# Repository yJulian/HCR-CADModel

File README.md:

From
https://github.com/open-dynamic-robot-initiative/master-board

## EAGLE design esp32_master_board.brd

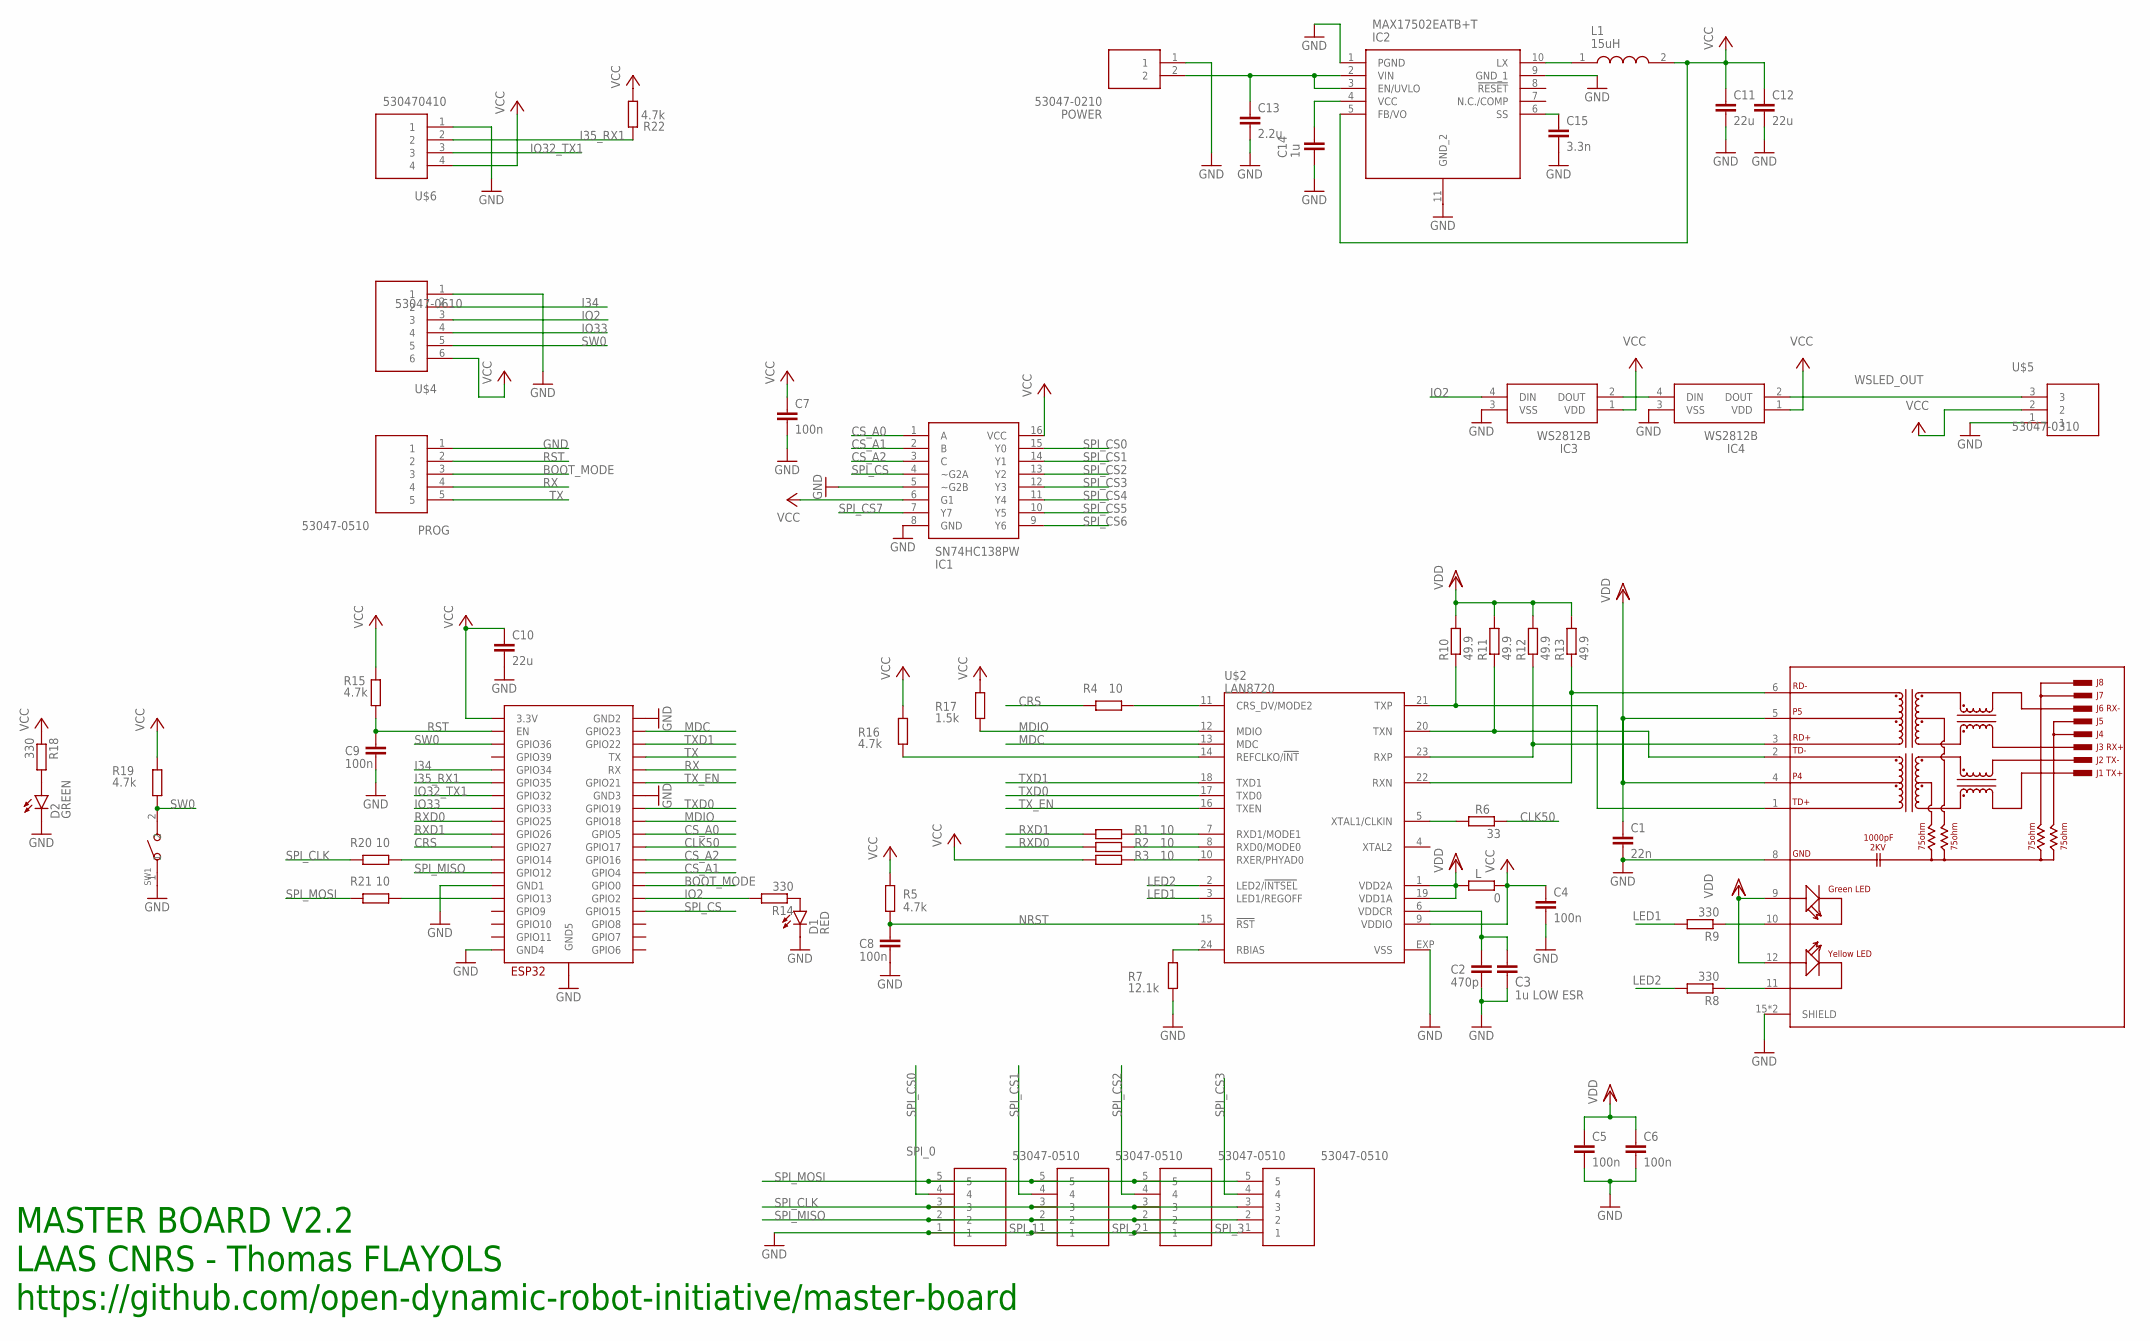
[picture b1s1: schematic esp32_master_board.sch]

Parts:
C1: 22n; 0402; MANUFACTURER_PART_NUMBER 885012205052
C2: 470p; 0402; MANUFACTURER_PART_NUMBER CL05C471JB5NNNC
C3: 1u LOW ESR; 0402; MANUFACTURER_PART_NUMBER CPL-CAP-X5R-0402-1UF-6.3V
C4, C5, C6, C7, C8, C9: 100n; 0402; MANUFACTURER_PART_NUMBER CPL-CAP-X7R-0402-100NF-16V
C10, C11, C12: 22u; C0805; MANUFACTURER_PART_NUMBER CPL-CAP-X5R-0805-22UF-6.3V
C13: 2.2u; C1210; MANUFACTURER_PART_NUMBER C3225X7R1H225K250AB
C14: 1u; 0402; MANUFACTURER_PART_NUMBER CPL-CAP-X5R-0402-1UF-6.3V
C15: 3.3n; 0402; MANUFACTURER_PART_NUMBER 885012205064
D1: RED; CHIPLED_0603; MANUFACTURER_PART_NUMBER CPL-LED-0603-RED
D2: GREEN; CHIPLED_0603; MANUFACTURER_PART_NUMBER CPL-LED-0603-GREEN
IC1: SN74HC138PW; SOP65P640X120-16N
IC2: MAX17502EATB+T; SON50P200X300X80-11N
IC3, IC4: WS2812B
L: 0; 0402; MANUFACTURER_PART_NUMBER CPL-RES-0402-0-0.063W
L1: 15uH; LPS6235
POWER: 53047-0210; 530470210; MANUFACTURER_PART_NUMBER DF13-3P-1.25DSA
PROG: 53047-0510; 530470510; MANUFACTURER_PART_NUMBER DF13-5P-1.25DSA
R1, R2, R3, R4, R20, R21: 10; 0402; MANUFACTURER_PART_NUMBER CPL-RES-0402-10-0.063W
R5, R15, R16, R19, R22: 4.7k; 0402; MANUFACTURER_PART_NUMBER CPL-RES-0402-4.7K-0.063W
R6: 33; 0402; MANUFACTURER_PART_NUMBER CRCW040233R0FKEDC
R7: 12.1k; 0402; MANUFACTURER_PART_NUMBER ERJ-U02F1212X
R8, R9, R14, R18: 330; 0402; MANUFACTURER_PART_NUMBER RC0402JR-13330RL
R10, R11, R12, R13: 49.9; 0402; MANUFACTURER_PART_NUMBER CRCW040249R9FKEDC
R17: 1.5k; 0402; MANUFACTURER_PART_NUMBER ERJ2GEJ152X
SPI_0, SPI_1, SPI_2, SPI_3: 53047-0510; 530470510; MANUFACTURER_PART_NUMBER DF13-5P-1.25DSA
SW1: B3U-1000P-2P-SMD; SW2-2.6-3.0X2.5X1.2+0.4MM; MANUFACTURER_PART_NUMBER B3U-1000P
U$1: ESP32-WROOM; MANUFACTURER_PART_NUMBER ESP32-WROOM-32D
U$2: LAN8720; QFN24; MANUFACTURER_PART_NUMBER LAN8720A-CP
U$3: HR911105A; HANRUN_HR911105A; MANUFACTURER_PART_NUMBER HR911105A
U$4: 53047-0610; 530470610; MANUFACTURER_PART_NUMBER DF13-6P-1.25DSA
U$5: 53047-0310; 530470310; MANUFACTURER_PART_NUMBER DF13-3P-1.25DSA
U$6: 530470410; MANUFACTURER_PART_NUMBER DF13-4P-1.25DSA

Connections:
BOOT_MODE: PROG.3, U$1.IO0 (GPIO0)
CLK50: R6.1, U$1.IO17 (GPIO17)
CRS: R4.1, U$1.IO27 (GPIO27)
CS_A0: IC1.1 (A), U$1.IO5 (GPIO5)
CS_A1: IC1.2 (B), U$1.IO4 (GPIO4)
CS_A2: IC1.3 (C), U$1.IO16 (GPIO16)
GND: C1.2, C2.2, C3.2, C4.2, C5.2, C6.2, C7.2, C8.2, C9.2, C10.2, C11.2, C12.2, C13.2, C14.1, C15.2, D1.C, D2.C, IC1.5 (~G2B), IC1.8 (GND), IC2.1 (PGND), IC2.9 (GND_1), IC2.11 (GND_2), IC3.3 (VSS), IC4.3 (VSS), POWER.1, PROG.1, R7.1, SPI_0.1, SPI_1.1, SPI_2.1, SPI_3.1, SW1.1, U$1.GND1, U$1.GND2, U$1.GND3, U$1.GND4, U$1.GND5, U$2.EXP (VSS), U$3.8 (GND), U$3.15 (SHIELD), U$3.16 (SHIELD), U$4.1, U$5.1, U$6.1
I34: U$1.IO34 (GPIO34), U$4.2
I35_RX1: R22.2, U$1.IO35 (GPIO35), U$6.2
IO2: IC3.4 (DIN), R14.2, U$1.IO2 (GPIO2), U$4.3
IO32_TX1: U$1.IO32 (GPIO32), U$6.3
IO33: U$1.IO33 (GPIO33), U$4.4
LED1: R9.2, U$2.3 (LED1/REGOFF)
LED2: R8.2, U$2.2 (LED2/!INTSEL)
MDC: U$1.IO23 (GPIO23), U$2.13 (MDC)
MDIO: R17.1, U$1.IO18 (GPIO18), U$2.12 (MDIO)
unnamed: R1.2, U$2.7 (RXD1/MODE1)
unnamed: R2.2, U$2.8 (RXD0/MODE0)
unnamed: R3.2, U$2.10 (RXER/PHYAD0)
unnamed: R4.2, U$2.11 (CRS_DV/MODE2)
unnamed: R6.2, U$2.5 (XTAL1/CLKIN)
unnamed: R7.2, U$2.24 (RBIAS)
unnamed: R10.1, U$2.21 (TXP), U$3.1 (TD+)
unnamed: R11.1, U$2.20 (TXN), U$3.2 (TD-)
unnamed: R12.1, U$2.23 (RXP), U$3.3 (RD+)
unnamed: R13.1, U$2.22 (RXN), U$3.6 (RD-)
unnamed: R8.1, U$3.11 (YC)
unnamed: R9.1, U$3.10 (GC)
unnamed: R16.1, U$2.14 (REFCLKO/!INT)
unnamed: C2.1, C3.1, U$2.6 (VDDCR)
unnamed: C14.2, IC2.4 (VCC)
unnamed: D1.A, R14.1
unnamed: R21.2, U$1.IO13 (GPIO13)
unnamed: IC2.10 (LX), L1.1
unnamed: IC3.2 (DOUT), IC4.4 (DIN)
unnamed: D2.A, R18.2
unnamed: R20.2, U$1.IO14 (GPIO14)
unnamed: C15.1, IC2.6 (SS)
unnamed: C13.1, IC2.2 (VIN), IC2.3 (EN/UVLO), POWER.2
NRST: C8.1, R5.1, U$2.15 (!RST)
RST: C9.1, PROG.2, R15.1, U$1.EN
RX: PROG.4, U$1.RX
RXD0: R2.1, U$1.IO25 (GPIO25)
RXD1: R1.1, U$1.IO26 (GPIO26)
SPI_CLK: R20.1, SPI_0.3, SPI_1.3, SPI_2.3, SPI_3.3
SPI_CS: IC1.4 (~G2A), U$1.IO15 (GPIO15)
SPI_CS0: IC1.15 (Y0), SPI_0.4
SPI_CS1: IC1.14 (Y1), SPI_1.4
SPI_CS2: IC1.13 (Y2), SPI_2.4
SPI_CS3: IC1.12 (Y3), SPI_3.4
SPI_CS4: IC1.11 (Y4)
SPI_CS5: IC1.10 (Y5)
SPI_CS6: IC1.9 (Y6)
SPI_CS7: IC1.7 (Y7)
SPI_MISO: SPI_0.2, SPI_1.2, SPI_2.2, SPI_3.2, U$1.IO12 (GPIO12)
SPI_MOSI: R21.1, SPI_0.5, SPI_1.5, SPI_2.5, SPI_3.5
SW0: R19.1, SW1.2, U$1.SENSOR_VP (GPIO36), U$4.5
TX: PROG.5, U$1.TX
TXD0: U$1.IO19 (GPIO19), U$2.17 (TXD0)
TXD1: U$1.IO22 (GPIO22), U$2.18 (TXD1)
TX_EN: U$1.IO21 (GPIO21), U$2.16 (TXEN)
VCC: C4.1, C7.1, C10.1, C11.1, C12.1, IC1.6 (G1), IC1.16 (VCC), IC2.5 (FB/VO), IC3.1 (VDD), IC4.1 (VDD), L.1, L1.2, R3.1, R5.2, R15.2, R16.2, R17.2, R18.1, R19.2, R22.1, U$1.3V3 (3.3V), U$2.9 (VDDIO), U$4.6, U$5.2, U$6.4
VDD: C1.1, C5.1, C6.1, L.2, R10.2, R11.2, R12.2, R13.2, U$2.1 (VDD2A), U$2.19 (VDD1A), U$3.4, U$3.5, U$3.9 (GA), U$3.12 (YA)
WSLED_OUT: IC4.2 (DOUT), U$5.3

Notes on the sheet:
MASTER BOARD V2.2 LAAS CNRS - Thomas FLAYOLS https://github.com/open-dynamic-robot-initiative/master-board

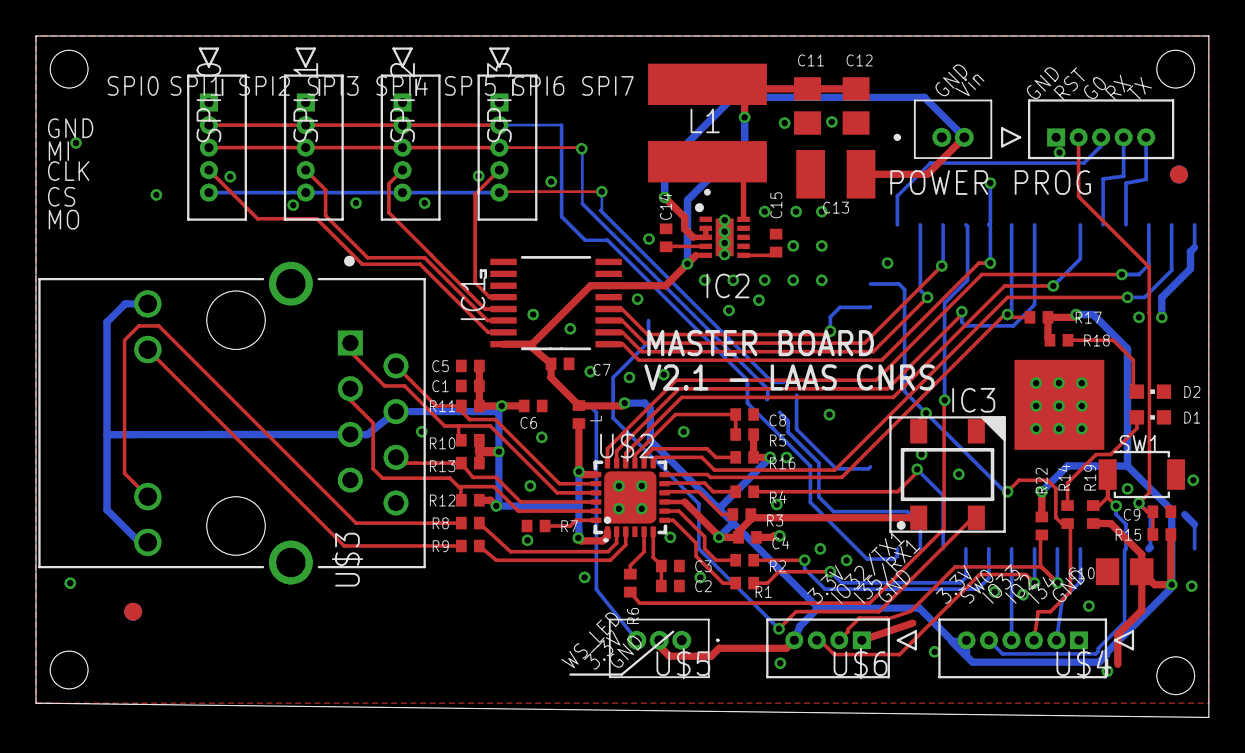
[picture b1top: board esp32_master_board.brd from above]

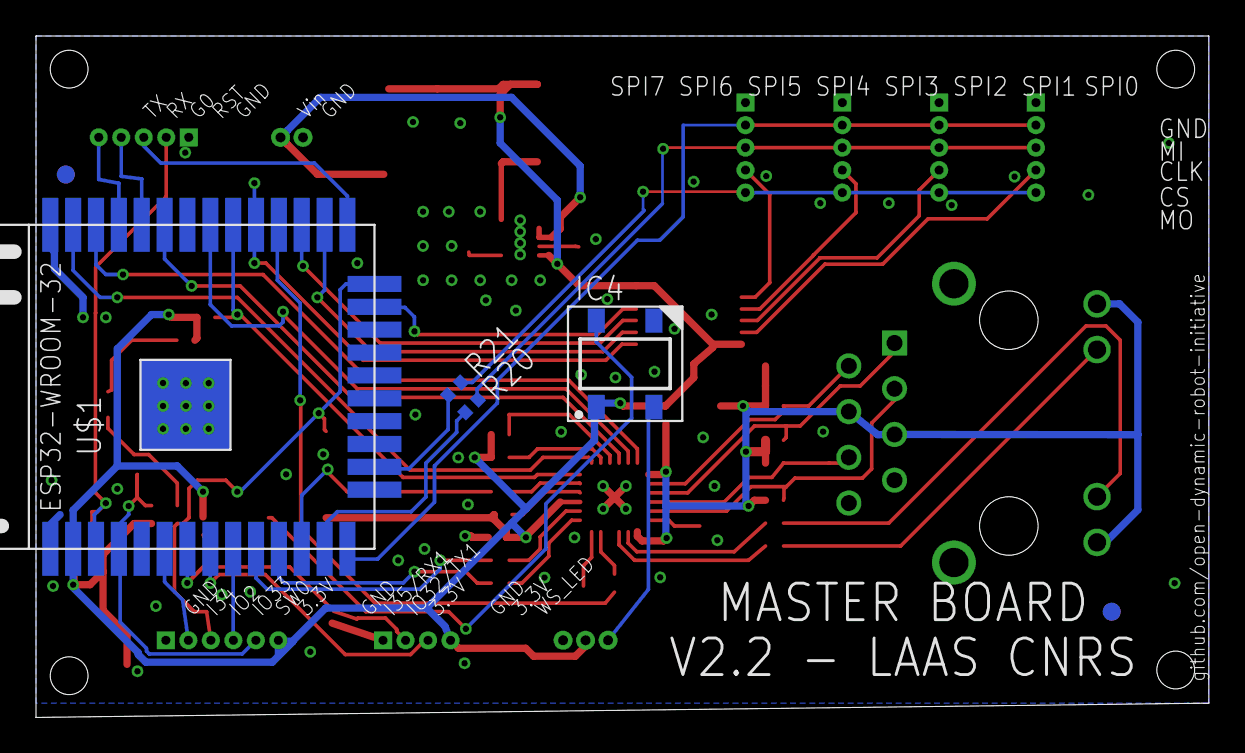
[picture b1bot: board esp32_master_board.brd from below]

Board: 2 copper layers, 65.2 x 37.9 mm, 62 parts (6 on the bottom side), 60 nets.

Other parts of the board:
REF1, REF2, REF3, REF4: VISION_REF10

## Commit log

2025-05-27 Initial
2025-07-24 Fusion Model

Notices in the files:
parts and their libraries:
microchip-smsc-lan8720: (C) 2014 Tomasz Boleslaw CEDRO, cederom@tlen.pl, http://www.tomek.cedro.info.
dicons: Copyright (C) 2004, Bob Starr (rtzaudio@mindspring.com)
